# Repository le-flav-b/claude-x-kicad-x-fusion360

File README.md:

<div align="center">

# A lamp designed end to end by AI

**I gave the prompts. Claude did the rest through its tool connections: the PCB in KiCad, a parametric enclosure in Fusion 360, the renders, the print files and the PCB order files.**

**3 chats with Claude · 1 image from ChatGPT · ~60 messages from me · ~900 tool calls by Claude**

</div>

---

## What is this?

A small battery lamp: a round 36 mm PCB with ten LEDs and a sun logo, held in a tilting head on a two-armed stand, with three AAA batteries hidden in the base.

The point of the project wasn't the lamp. I wanted to see how far an AI could get with **real engineering tools** while I stayed in the chat. I didn't draw a schematic, route a trace or sketch a profile. Claude drove KiCad and Fusion 360 directly, through MCP servers (connections that let it call the apps' own functions), and I described what I wanted, answered its questions and pushed back when I disagreed.

This README tells how that went, chat by chat, including the parts where I had to step in.

```mermaid
flowchart LR
    A["💬 Chat 1<br/>Connect Claude to KiCad"] --> B["💬 Chat 2<br/>Design the PCB"]
    B --> C["🖐️ Me<br/>Import the PCB into Fusion"]
    D["🎨 ChatGPT<br/>One inspiration image"] --> E
    C --> E["💬 Chat 3<br/>Design the enclosure"]
    E --> F["💬 Same chat<br/>Screenshots, renders,<br/>STL and Gerber files"]
    F --> G["📝 This README<br/>Written from the chat exports"]
```

| Chat | When | My messages | Claude's tool calls | Result |
|---|---|---|---|---|
| **KiCad MCP tools setup** | Oct 17 | 22 | 41 | Claude can drive KiCad |
| **LED circuit KiCad project** | Oct 17 and Nov 11 | 31 | 485 (366 in KiCad) | 36 mm PCB, ERC and DRC fully clean |
| **Fusion360 lamp enclosure design** | Nov 12 | 7 | 390 (225 in Fusion 360) | Enclosure, renders, videos, every file to build it |

---

## Chapter 0: Teaching Claude to use KiCad

My very first message was a test:

> *"Show me what you can do in Kicad. I just created a new project and opened the schematic and PCB editors. Use the KiCad MCP tools to create a simple schematic and PCB of your choice."*

Claude's answer: it couldn't, because it had no KiCad tools. So the first chat turned into two hours of setup.

1. **Install the bridge.** I installed [Konnect](https://github.com/mixelpixx/Konnect), an open-source MCP server for KiCad, as a KiCad plugin, and turned on the KiCad API in the preferences.
2. **Register it with Claude.** It goes in the `mcpServers` section of the Claude desktop app's config file. That took several tries: my first file was in the wrong folder, and the Microsoft Store version of the app keeps its config in yet another one.
3. **Tools appeared, but only a few.** Konnect starts with a small starter set and loads the rest on demand, and the Claude app only reads the tool list once, when it connects. Claude could open a schematic viewer, but it couldn't place a single component.
4. **I pushed back.** Claude suggested switching to a little-known fork built around this problem. I wasn't convinced:

   > *"But are you sure about this ? We are talking about a 5 stars fork of a 1.2k stars project.. Why don't konnect works and why would kicad-agentic-mcp work ?"*

   Claude backed down and admitted it had been guessing. I asked it to dig through Konnect's issues and docs instead, and it found the fix in Konnect's own troubleshooting guide: one setting, `"eager_toolsets": true`.
5. **I started a fresh chat**, and Claude had all 228 KiCad tools.

> [!TIP]
> **If you want to try this:** set `"eager_toolsets": true` in Konnect's `settings.json`, **start KiCad before the Claude desktop app** (Konnect picks up KiCad's API socket when it launches), and open a new chat after you change any tool setup.

---

## Chapter 1: The PCB in KiCad

The second chat started from the prompt Claude had drafted for me at the end of the setup chat:

> *"Use the Konnect tools to build a small example in my KiCad project: a simple LED circuit (connector, resistor, LED) in the schematic, run ERC, then sync it to the PCB, add a small board outline, place and route the footprints, and run DRC."*

Six minutes and 59 tool calls later there was a schematic, a routed board, **ERC 0 errors, DRC 0 errors**. Then it got interesting.

<table>
<tr>
<td width="50%"></td>
<td width="50%"></td>
</tr>
<tr>
<td align="center"><sub>Schematic: J1 feeds ten resistor and LED branches</sub></td>
<td align="center"><sub>Board: single copper layer, VIN disc in the centre, ground pour around it</sub></td>
</tr>
</table>

### How the board evolved, one prompt at a time

| I said | Claude did |
|---|---|
| *"now I want 10 LEDs arranged in a circle. Also add the 3d models if you can"* | 21 parts on a 70 mm round board, 41 routed segments, 3D models, a STEP export. KiCad's API refused non-90° rotations of these footprints, so it asked me before snapping them to 90°. |
| *"reduce the PCB size, add a ground plane, get rid of the sharp angles … align everything nicely with proper angles, including the silkscreen"* | Proposed a two-layer board with a ground plane on the back. |
| *"Am I understanding that you're gonna use 2 layers? I don't think that's necessary."* | Agreed and redesigned it on **one layer**: a VIN pour in the middle, a ground pour around it and ten straight radial traces. That's ten vias, ten stubs and a copper layer fewer. To get true radial angles it wrote the rotations straight into the board file while KiCad was closed. |
| *"I want a smaller board … the names of the LEDs to face the outside … And I want a little sun logo in the middle … with twice the rays, the one in the same line as the components being a little smaller"* | A 36 mm board, and a sun footprint generated from scratch: 20 rays, short ones on the component axes and long ones between them. |
| *"something to attach the PCB to a future 3D print, and … the connector to be mounted in the back"* | Five M2 mounting holes in the gaps between LEDs, the LED ring renumbered clockwise from the connector, and the connector's 3D model moved under the board. |
| *"I don't want any error nor warning"* | Sorted the 37 warnings into three kinds of metadata mismatch and told me which KiCad menu clears each one. |
| *"rename the LEDs D0 to D9"* + *"the resistors should also be from 0 to 9"* | Renamed all 20 parts, rerouted and relabelled. Final result: **DRC 0 errors, 0 warnings, 0 unconnected.** |

### Where KiCad still needed my hands

Some things had no Konnect tool, or KiCad's API refused them. Each time, Claude stopped and gave me the exact click to make:

- **Close or reopen KiCad** at the right moments. Rotations the API won't do can only be written to the file while KiCad is closed, and an open schematic editor locks its file.
- **Restart the Claude app** after a safety guard in Konnect refused to write to a board it had seen open in KiCad.
- In the PCB editor: delete two copper zones, hide the reference designators, drop the sun footprint in place, run *Update PCB from Schematic* (F8) and *Update Footprints from Library*, and press Escape when a leftover tool kept KiCad busy.

Claude also owned its mistakes. When one of its suggested fixes wiped the connector's 3D placement, it said so (*"My fault for not sequencing those"*), redid the placement with the sign corrected, and put that step last so nothing else could undo it.

At the end it even tried to publish the project. After I signed in to GitHub in the app's built-in browser, it created a repository by itself, but couldn't push to it. So I created this repo and pushed the KiCad files myself.

---

## Interlude: From PCB to idea

Two steps happened outside Claude:

1. **I imported the PCB into Fusion 360** by hand, and created an empty *Enclosure* component next to it.
2. **I asked ChatGPT for a picture** of what the lamp could look like. That single image ([`chat-gpt-design-inspiration.png`](assets/chat-gpt-design-inspiration.png)) was the whole design brief for the look.

---

## Chapter 2: The enclosure in Fusion 360

This was the prompt for the third chat, word for word:

> *"I want you to make an enclosure for a lamp in Fusion360 for the PCB we made earlier in KiCad with another chat. I've asked ChatGPT to render an image that I put in this folder. Use it as an inspiration. […] The features of the lamp are a rotative base, an inclinable head, and a place behind the PCB to put the batteries and the ON/OFF switch. Nothing cover the PCB, and the 5 mounting screws will use threaded brass inserts. The model has to be 3D printable in multiple parts that are easily assembled in the way you prefer. You need to create different component for the head, the body, and the base […]. All your sketches needs to be fully constrained and your design should be parametric, using references to previous dimensions when it's appropriate. **Before starting, ask me every questions you need to clear** and if at any point you doubt, feel free to stop and ask."*

### First, questions

Claude looked at the image and the Fusion design, then asked its questions as multiple-choice cards:

| Question | My answer |
|---|---|
| Power source? | 3 × AAA, in the base (the resistor values can change) |
| Battery holder? | An off-the-shelf 48 × 35 × 13 mm holder |
| ON/OFF switch? | A round 2-position switch, behind the head |
| How does the head hold its angle? | A 3D-printed screw |
| Overall size? | About 100 mm tall |
| Where does the cable go? | Hidden inside one arm |
| Battery access? | A snap-fit lid |
| Rotating base? | *"I don't want a rotative base anymore"* |

### First build, then one round of corrections

The first version took 118 tool calls: Head, Body, Base, a base lid and two tilt screws as separate components, every sketch fully constrained and driven by user parameters. My reply started *"That's a great design, but here's some fixes"* and listed what I wanted changed:

<details>
<summary><b>My correction prompt</b> (click to expand)</summary>

> The overall design should be softer, with more rounded or chamfered edges, less aggressive screw heads pattern...
>
> There should be a hole under the base lid to make it easier to remove because the little thing you made in the back won't be enough.
>
> It will be too hard to pass the electric wire in the arm with those 90 degrees angles.
>
> The joint is bad, its motion is set to rigid, and even when I changed it by hand the screw doesn't move with it as they should since they're screw down to the head.
>
> The threaded brass insert holes are not 3D printable since they are floating in the air, they should either have a start from below on the whole with a 45 degrees angle or go until the back of the head.
>
> I want you to add curved texts on the top of the base that goes around it. One in the front saying something like "Designed end to end by Claude with KiCad and Fusion360". One in the back saying "FLAVIEN BOULEAU 2026".
>
> I want you to add the mechanical parts: screws, batteries and battery holder, ON/OFF switch, inserts, and cable.
>
> I want you to add the appearance.

</details>

Claude worked through all of it in one go (80 tool calls). It gave the design rounder edges, put a finger hole in the lid, gave the arm channel smooth bends, made the tilt joint actually drive the head with the screws following it, and gave the brass insert bosses 45° bases so they print without supports. It also added the curved engraved texts, modelled every part from the hardware list and applied the appearances.

<table>
<tr>
<td width="50%"></td>
<td width="50%"></td>
</tr>
<tr>
<td align="center"><sub>Curved text engraved on the base</sub></td>
<td align="center"><sub>Lid removed: battery holder and cells</sub></td>
</tr>
</table>

### The cable problem: a real design conversation

The modelled cable didn't bend when the head tilted. I asked *"Is there a way to fix that ?"*. While Claude worked out the geometry of the loop, it found a real mechanical problem: a cable leaving the arm and entering the head at different points gets pulled or crushed as the head turns.

Its first explanation was too abstract (*"Sorry, that was too abstract. Here's what I mean"*), so it drew a diagram right in the chat. I still challenged it: *"Can't you just make the cable exit further down the arm?"*, then *"Why can't it enter the head at the same place?"*. That led to the best answer: **run the cable through the hollow tilt screw, along the pivot axis**, where turning the head doesn't stretch it at all.

<table>
<tr>
<td width="50%"></td>
<td width="50%"></td>
</tr>
<tr>
<td align="center"><sub>Section through the tilt axis: the cable runs through the arm channel and the hollow screw</sub></td>
<td align="center"><sub>X-ray side view of the cable route</sub></td>
</tr>
</table>

### What's inside the model

- **Fully parametric:** user parameters drive the sizes, and changing `print_clear` (0.2 mm) re-fits every printed thread and gap.
- **Fully constrained sketches**, with a clean timeline you can replay (below).
- **Printable without supports:** each part has its own print orientation, and the inserts sit in 45° bosses.
- **Real hardware:** 7 brass inserts, M2 screws, the battery holder, the switch and a routed cable, all as components with joints. The PCB and screws follow the head through its full ±90° of tilt.

<p align="center">
  <br>
  <sub>The Fusion 360 timeline replayed: 149 steps, every feature placed by Claude</sub>
</p>

---

## Chapter 3: Documentation in a single prompt

> *"Now can you create a folder `assets` and put inside a lot of screenshots to document everything. I want screenshots of KiCad (schematics, pcb editor, pcb 3d viewer) and Fusion360 (a lot with different components visibility, light source, angle of the head, section analysis, components colors, video of history playing, ... every interesting combination). Then make a folder `export` and download there all the STL parts I need to print. […] You can also export from kicad everything needed for the PCB order and put it in `export`."*

From that one message, Claude produced:

- **52 Fusion viewport captures**: every angle, tilt steps from -90° to +90°, X-ray views, section analyses, colours per component and visual styles.
- **10 ray-traced renders** with different lighting environments.
- **3 videos**: a turntable, a tilt sweep and the timeline replay.
- **KiCad screenshots.** For these it used computer use, with my permission, to drive KiCad's windows and its 3D viewer.
- **5 STL files**, already in print orientation and checked to be watertight.
- **The PCB order package**: Gerbers, a ZIP ready for JLCPCB, the BOM, the pick-and-place file and the schematic as a PDF.

<table>
<tr>
<td width="50%"></td>
<td width="50%"></td>
</tr>
<tr>
<td width="50%"></td>
<td width="50%"></td>
</tr>
</table>

The full index is in [`assets/README.md`](assets/README.md).

---

## What I actually did

Here's the full list of what I did myself:

1. **Setup:** installed KiCad 10 and the Konnect plugin, edited two config files, and restarted the apps when asked. Fusion 360 was connected to Claude through its own MCP server.
2. **Prompting:** about 60 messages over three chats, counting short ones like *"go"*.
3. **Answering questions and pushing back**, which made a real difference twice: the single-layer board and the cable through the pivot.
4. **A dozen clicks in KiCad** that the tools couldn't do (listed in Chapter 1).
5. **Bridging the apps:** importing the PCB into Fusion 360 and asking ChatGPT for one image.
6. **Small touches:** a couple of appearance colours in Fusion, saving the design, and the git commits.
7. **For this README:** exporting my chat history so Claude could read the earlier chats.

## What the chats felt like

- **Claude asked before it built.** The enclosure chat opened with a set of multiple-choice questions, and the PCB chat paused whenever a choice was really mine to make (snapping parts to 90°, the board size, whether to rename the resistors too).
- **It checked its own work and showed the numbers:** ERC and DRC counts after every change, pad coordinates checked against its predictions, a collision check of the head at real tilt angles, and watertight checks on the STL files.
- **It said clearly when a tool couldn't do something,** explained why, and handed me the exact click. It didn't pretend.
- **Pushing back worked.** Both of my "are you sure?" moments made the result better.
- **These were long working sessions, not one-shot prompts.** The setup took an afternoon of trial and error. The PCB and enclosure chats each made hundreds of tool calls and ran for hours, mostly without me.

---

## Repository map

```
.
├── claude-x-kicad-x-fusion360.kicad_pro / .kicad_sch / .kicad_pcb   KiCad project
├── claude-x-kicad-x-fusion360.f3d                                   Fusion 360 design (enclosure + PCB)
├── desktop.ini                         Windows folder icon (points to assets/icon/folder.ico)
├── sunlogo.pretty/                     The generated sun logo footprint
├── assets/                             Screenshots, renders, videos, inspiration image
│   ├── kicad/   fusion/   fusion/renders/   fusion/videos/
└── export/                             Everything needed to build it
    ├── stl/                            5 print-ready parts
    ├── pcb/                            Gerbers, JLCPCB ZIP, BOM, pick-and-place, schematic PDF
    └── pcb.step                        3D model of the assembled PCB
```

## Build one

Everything is in [`export/`](export/README.md): STL files with print settings, PCB order files, the hardware list (inserts, M2 screws, AAA holder, switch, cable) and the assembly steps.

## Project history

Every step was committed on November 12, 2026 (UTC+8). The PCB itself was designed in two earlier sessions, on October 17 and November 11.

| Commit | Time | Step |
|---|---|---|
| [`db6db27`](https://github.com/le-flav-b/claude-x-kicad-x-fusion360/commit/db6db27) | 13:54 | PCB by Claude with KiCad (from two earlier chats) |
| [`cf27203`](https://github.com/le-flav-b/claude-x-kicad-x-fusion360/commit/cf27203) | 14:36 | Manual import of the PCB in Fusion 360 |
| [`0bd1962`](https://github.com/le-flav-b/claude-x-kicad-x-fusion360/commit/0bd1962) | 15:07 | Design inspiration by ChatGPT |
| [`277b937`](https://github.com/le-flav-b/claude-x-kicad-x-fusion360/commit/277b937) | 19:12 | 3D design after the first prompt, by Claude with Fusion 360 |
| [`0096e14`](https://github.com/le-flav-b/claude-x-kicad-x-fusion360/commit/0096e14) | 22:23 | 3D design after two correction prompts |
| [`870d102`](https://github.com/le-flav-b/claude-x-kicad-x-fusion360/commit/870d102) | 23:09 | Renders, screenshots, videos and exports, all from a single prompt |
| [`e0e7deb`](https://github.com/le-flav-b/claude-x-kicad-x-fusion360/commit/e0e7deb) | 23:43 | This README, written by Claude from the chat exports |

---

<div align="center">
<sub>Designed by Flavien Bouleau with Claude, 2026. This README was written by Claude as well, from exports of the three chats.</sub>
</div>

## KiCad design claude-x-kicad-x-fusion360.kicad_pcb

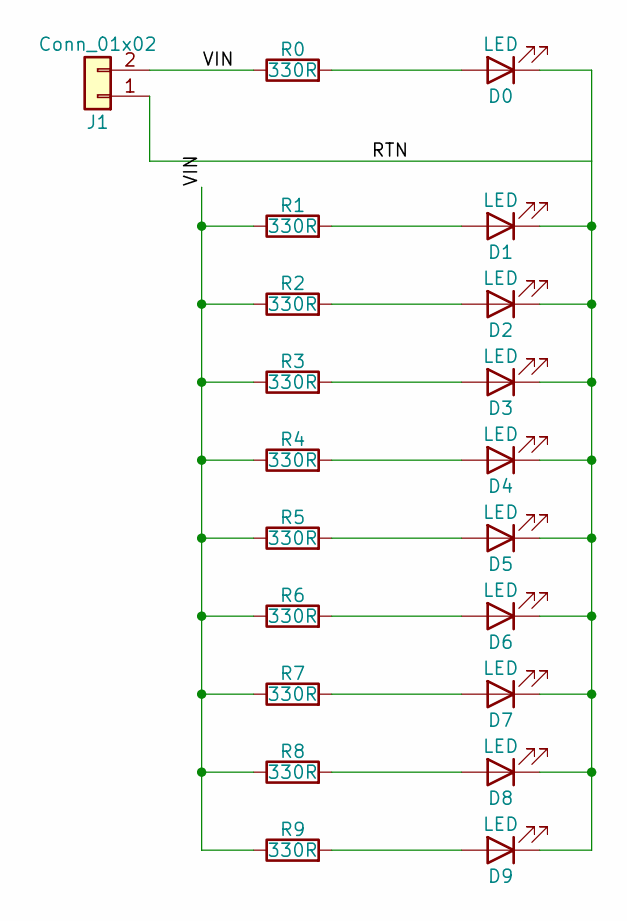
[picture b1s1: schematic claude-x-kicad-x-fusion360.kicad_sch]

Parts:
D0, D1, D2, D3, D4, D5, D6, D7, D8, D9: LED; LED_0805_2012Metric
J1: Conn_01x02; PinHeader_1x02_P2.54mm_Vertical
R0, R1, R2, R3, R4, R5, R6, R7, R8, R9: 330R; R_0805_2012Metric

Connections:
/RTN: D0.1 (K), D1.1 (K), D2.1 (K), D3.1 (K), D4.1 (K), D5.1 (K), D6.1 (K), D7.1 (K), D8.1 (K), D9.1 (K), J1.1
/VIN: J1.2, R0.1, R1.1, R2.1, R3.1, R4.1, R5.1, R6.1, R7.1, R8.1, R9.1
unnamed: D0.2 (A), R0.2
unnamed: D1.2 (A), R1.2
unnamed: D2.2 (A), R2.2
unnamed: D3.2 (A), R3.2
unnamed: D4.2 (A), R4.2
unnamed: D5.2 (A), R5.2
unnamed: D6.2 (A), R6.2
unnamed: D7.2 (A), R7.2
unnamed: D8.2 (A), R8.2
unnamed: D9.2 (A), R9.2

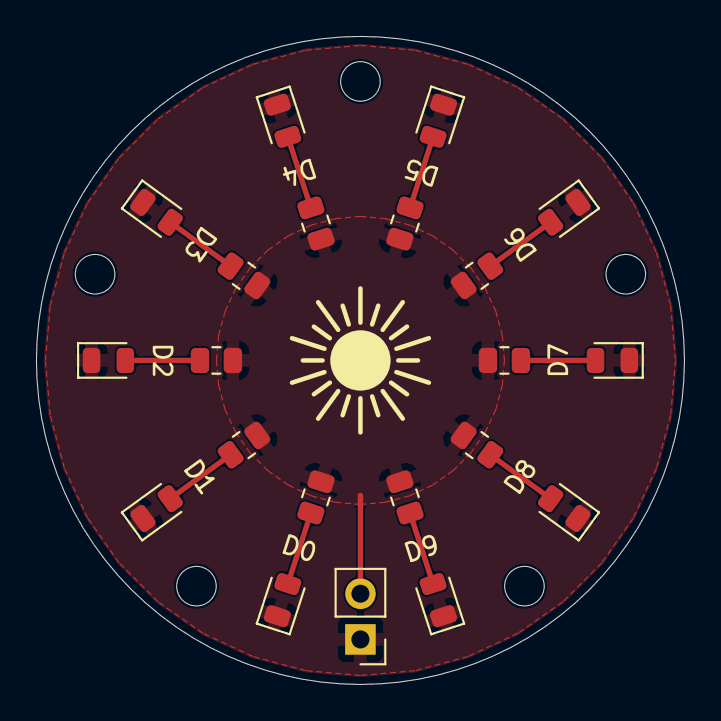
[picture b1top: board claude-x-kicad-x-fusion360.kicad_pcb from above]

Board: 2 copper layers, 36.0 x 36.0 mm, 26 parts (0 on the bottom side), 12 nets.

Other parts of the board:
H1, H2, H3, H4, H5: MountingHole_2.2mm_M2
